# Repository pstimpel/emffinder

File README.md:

# EMF Finder / EMF Detector 2.0
## 3d Printed arduino based emf detector

License: https://creativecommons.org/licenses/by-nc-sa/4.0/

The result of this project is a 3D printed, arduino nano driven EMF detector. Yes, you could go for hunting ghosts, or you could try to find sources of electro magnetic fields creating noise in your speakers, or killing the functionality of your gadgets.

### Project URLs

https://www.prusaprinters.org/prints/21355-emf-finder-detector-20

https://pinshape.com/items/59651-3d-printed-emf-finder-detector-20

https://www.thingiverse.com/thing:4153746

## Why do we need another one?

Yes, this project is based on some videos I found. However, I thought I could push it further. This design does only use one resistor to drive all of the LEDs, other designs were using 10 of those, which is kind of a waste. And, I thought it would be cool to be able to change the sensitivity. So I added a switch to do exactly that.

## Video introduction

## What we need

### Electrics/electronics
- Arduino Nano 3.0 5V (https://www.amazon.de/Anpro-Entwicklerboard-Atmega328P-Arduino-EINWEG/dp/B07H2VT2JN/)
- 10 red LED 5mm (https://www.reichelt.de/led-5-mm-bedrahtet-rot-fr-led-5-rd-dif-p230933.html)
- 1 resistor 3.3 MOhm (https://www.reichelt.de/widerstand-kohleschicht-3-3-mohm-0207-250-mw-5-1-4w-3-3m-p1398.html)
- 1 resistor 330 Ohm (https://www.reichelt.de/widerstand-kohleschicht-330-ohm-0204-0-125-w-5-k-o-rd18jn331t52-p237355.html)
- 1 Diode 1N4001 (https://www.reichelt.de/gleichrichterdiode-50-v-1-a-do-41-1n-4001-p1723.html)
- Buzzer 5 Volts (https://www.amazon.de/gp/product/B073RH8TQK/), we need the bigger one out of the package
- 2 switches (https://www.amazon.de/gp/product/B07MY2WVQ3)
- some strand wire, about 400 mm (https://www.amazon.de/gp/product/B01BI1G88C)
- some more heavy wire, about 500 mm, for our antenna. It should maintain its form if you bend it!
- 4 screw terminals, 5mm, 2 pins (https://www.amazon.de/gp/product/B07K31L4FH/)
- battery connector for 9V batteries (https://www.amazon.de/Neuftech®-Batterie-Anschluss-Anschlusskabel-schwarz/dp/B00YTRNLGU/)
- a 9V battery (https://www.amazon.de/Varta-Longlife-Batterie-Alkaline-Batterien/dp/B004WYN62O/)
- stuff to create a pcb, or a supplier for your pcb
- soldering stuff

### 3D-printing
- pla filament of your choice, I was using https://dasfilament.de - which is my favorite supplier
- a 3d printer

### Tools, other stuff
- 11 screws M3x8, cylinder head (https://www.schrauben-paul.com/DIN-912-Zylinderkopfschraube-Edelstahl-A2-ISK-M-3-x-8-Inhalt-100-Stk)
- 1 screw M3x8, countersunk (https://www.schrauben-paul.com/ISO-10642-Maschinenschraube-Innensechskant-Edelstahl-A2-M-3x8-Inhalt-100-Stk)
- screwdriver

##  How to assemble
First we need to create the PCB. You can do it yourself which I find is much fun. Or you could send the files to your favorite supplier. 

Once you received the board, you have to solder the parts to it. Put the board in front of you, copper side down, two big holes upwards. I suggest you this order, but put the Arduino sketch onto your Arduino before soldering it to the board:

1. Resistors
2. Diode
3. Arduino
4. Buzzer
5. Screw Terminals
6. LEDs

Make sure not to confuse the direction of some parts.

1. Arduino: USB faces to the right
2. Buzzer: the longer poin is +, facing upwards
3. Diode: ground points upwards
4. LEDs: shorter pin is ground, point downwards

Next, 3D print the items. I was using a .4 nozzle on my Prusa I3 Mk3. I used 0.3 layer hight, 3 shells horizontal and vertical, and 10% cubic infill. No support needed.

Now mount the PCB into the Base, using 3 screws M3x8 cylinder head. Solder 2 100mm wires to the switch, repeat this for the second switch. Mount the switches into their position of the Base.

Cut the more heavy wire into half, and use something small like a small pencil to create your antennas by fiddling the wire around the pencil. Do this twice, and cut 3cm of the isolation if each antenna wire. 

Connect it to each other, and mount it into the 3D printed Antenna piece. Now, push it through the big hole at the upper side of the base. Connect it to the left connector of the screw terminal top/middle of the PCB. Use 2 M3x8 cylinder head screw to mount Antenna to Base.

Connect the On/Off switch to the left side, upper screw terminal.

Connect the Range switch to the top right screw terminal.

Connect the battery connector to the left screw terminal, left side, bottom. Ground is the upper connector, voltage is the connector downwards.

Time for a first test. Connect the battery, switch your device on using the upper switch. You see the LEDs flickering? If not, approach something like a TV, or mobile phone. Using the lower switch, you can switch between two ranges of sensitivity.

If all works as expected, put the Top onto the Base, and use 6 M3x8 cylinder head screws to close your device. 

Finally, put the battery into its place, and close the battery case useing the Cover, and the M3x8 countersunk screw.

Done!

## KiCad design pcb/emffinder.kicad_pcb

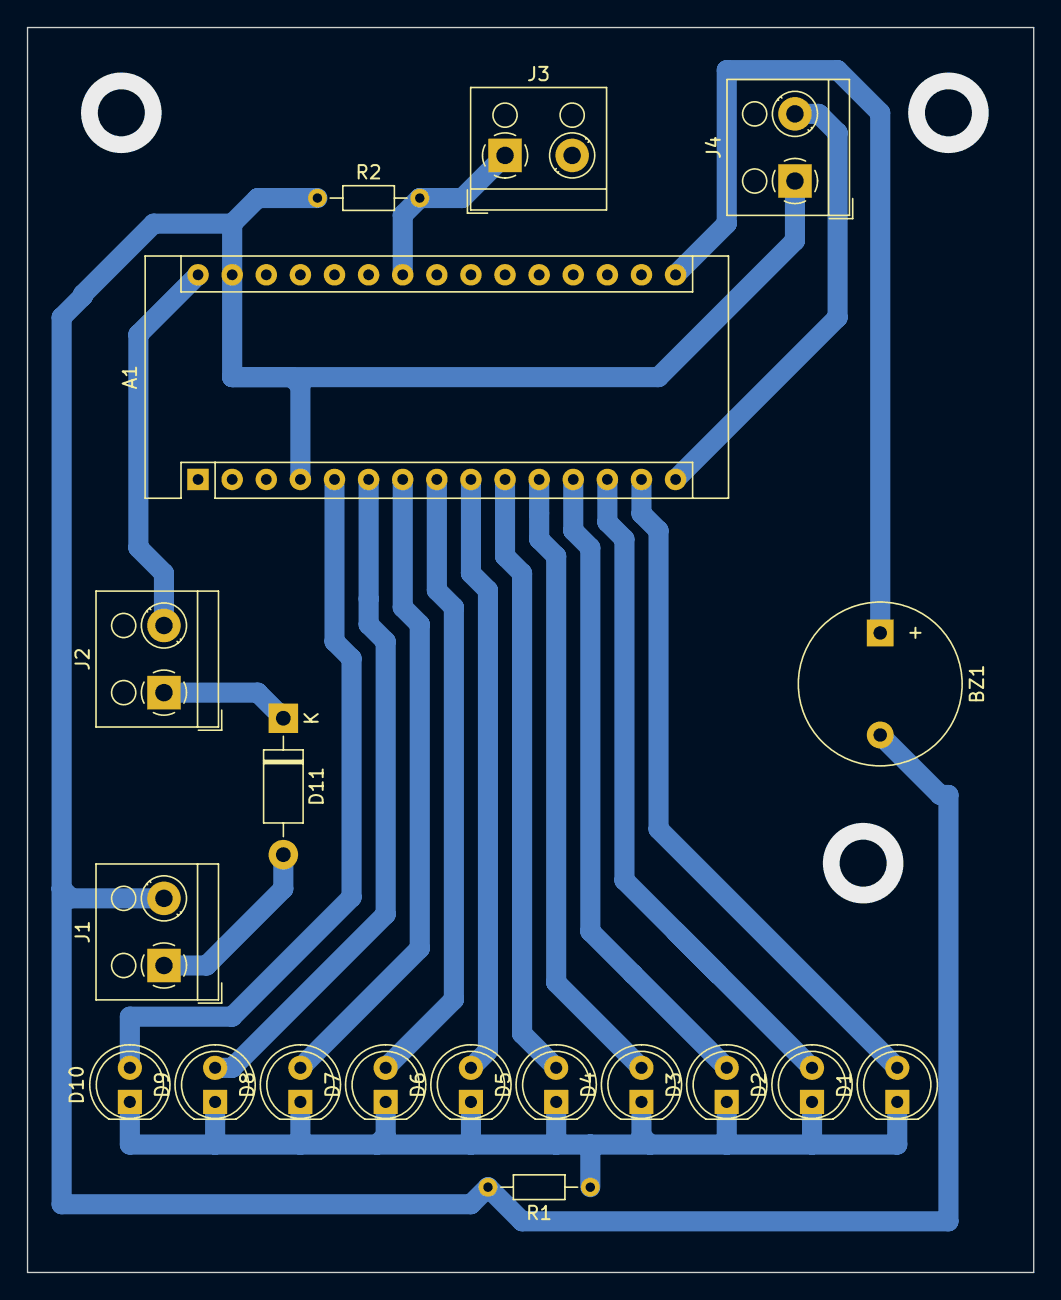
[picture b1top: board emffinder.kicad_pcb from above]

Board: 2 copper layers, 74.9 x 92.7 mm, 19 parts (0 on the bottom side), 18 nets.

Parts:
A1: ArdNano3; Arduino_Nano
BZ1: Buzzer; Buzzer_12x9.5RM7.6
D1, D2, D3, D4, D5, D6, D7, D8, D9, D10: L; LED_D5.0mm
D11: 1N4007; D_DO-41_SOD81_P10.16mm_Horizontal
J1: Power; TerminalBlock_RND_205-00001_1x02_P5.00mm_Horizontal
J2: SwitchPower; TerminalBlock_RND_205-00001_1x02_P5.00mm_Horizontal
J3: Antenna; TerminalBlock_RND_205-00001_1x02_P5.00mm_Horizontal
J4: SwitchRange; TerminalBlock_RND_205-00001_1x02_P5.00mm_Horizontal
R1: 330Ohm; R_Axial_DIN0204_L3.6mm_D1.6mm_P7.62mm_Horizontal
R2: 3.3 MOhm; R_Axial_DIN0204_L3.6mm_D1.6mm_P7.62mm_Horizontal

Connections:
unnamed: A1.5, D10.2
unnamed: A1.6, D9.2
unnamed: A1.7, D8.2
unnamed: A1.8, D7.2
unnamed: A1.9, D6.2
unnamed: A1.10, D5.2
unnamed: A1.11, D4.2
unnamed: A1.12, D3.2
unnamed: A1.13, D2.2
unnamed: A1.14, D1.2
unnamed: A1.15, J4.2
unnamed: A1.16, BZ1.1
unnamed: A1.24, J3.1, R2.2
unnamed: A1.4, A1.29, BZ1.2, J1.2, J4.1, R1.2, R2.1
unnamed: A1.30, J2.2
unnamed: D1.1, D2.1, D3.1, D4.1, D5.1, D6.1, D7.1, D8.1, D9.1, D10.1, R1.1
unnamed: D11.1, J2.1
unnamed: D11.2, J1.1

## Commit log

2020-02-09 Initial media, stl, arduino sketch and kicad board/circuit
2020-02-09 3mf file, circuit scheme and license
2020-02-09 Final V1
